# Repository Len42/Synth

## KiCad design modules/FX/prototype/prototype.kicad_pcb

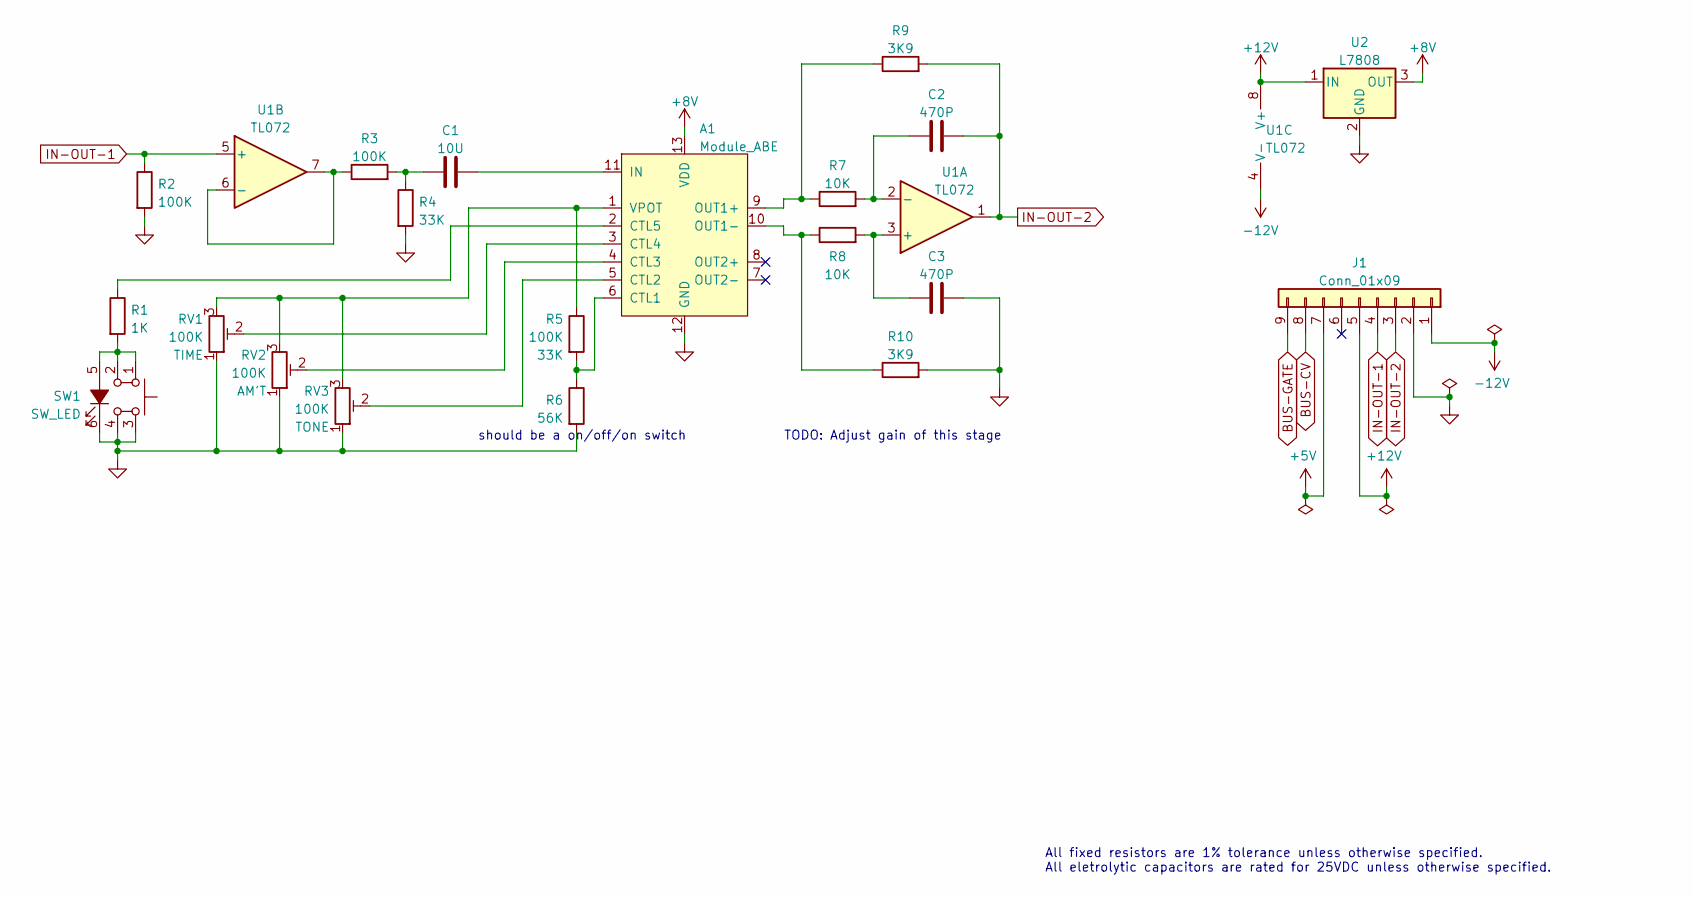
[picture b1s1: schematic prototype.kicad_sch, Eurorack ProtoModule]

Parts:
A1: Module_ABE; Module_ABE_Vert; ManufacturerPartNum ABE
C1: 10U; C_Radial_D5.0mm_H5.0mm_P2.50mm; ManufacturerPartNum ECE-A1EN100UI
C2, C3: 470P; C_Disc_D5.0mm_W2.5mm_P2.50mm
J1: Conn_01x09; PinHeader_1x09_P2.54mm_Vertical
R1: 1K; SB_Gen_4; ManufacturerPartNum MFR-12*
R2: 100K; SB_Gen_1; ManufacturerPartNum MFR-12*
R3: 100K; R_Axial_DIN0207_L6.3mm_D2.5mm_P7.62mm_Horizontal; ManufacturerPartNum MFR-12*
R4: 33K; SB_Gen_1; ManufacturerPartNum MFR-12*
R5: 100K; SB_Gen_5; ManufacturerPartNum MFR-12*
R6: 56K; SB_Gen_1; ManufacturerPartNum MFR-12*
R7, R8: 10K; R_Axial_DIN0207_L6.3mm_D2.5mm_P7.62mm_Horizontal; ManufacturerPartNum MFR-12*
R9: 3K9; SB_Gen_4; ManufacturerPartNum MFR-12*
R10: 3K9; R_Axial_DIN0207_L6.3mm_D2.5mm_P7.62mm_Horizontal; ManufacturerPartNum MFR-12*
RV1, RV2, RV3: 100K; Potentiometer_Bourns_3310R_Top
SW1: SW_LED; Breakout_SW_Push_LED_C&K_D6R; ManufacturerPartNum D6RLBUF1 LFS
U1: TL072; DIP-8_W7.62mm; ManufacturerPartNum TL072BCP
U2: L7808; TO-220-3_Vertical

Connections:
+5V: J1.7
+8V: A1.13 (VDD), U2.3 (OUT)
+12V: J1.5, U1.8 (V+), U2.1 (IN)
-12V: J1.1, U1.4 (V-)
BUS-CV: J1.8
BUS-GATE: J1.9
GND: A1.12 (GND), C3.2, J1.2, R2.2, R4.2, R6.2, R10.2, RV1.1, RV2.1, RV3.1, SW1.3, SW1.4, SW1.6 (K), U2.2 (GND)
IN-OUT-1: J1.4, R2.1, U1.5 (+)
IN-OUT-2: C2.2, J1.3, R9.2, U1.1
unnamed: A1.1 (VPOT), R5.1, RV1.3, RV2.3, RV3.3
unnamed: A1.2 (CTL5), R1.1
unnamed: A1.3 (CTL4), RV1.2
unnamed: A1.4 (CTL3), RV2.2
unnamed: A1.5 (CTL2), RV3.2
unnamed: A1.6 (CTL1), R5.2, R6.1
unnamed: A1.9 (OUT1+), R7.1, R9.1
unnamed: A1.10 (OUT1-), R8.1, R10.1
unnamed: A1.11 (IN), C1.2
unnamed: C1.1, R3.2, R4.1
unnamed: C2.1, R7.2, U1.2 (-)
unnamed: C3.1, R8.2, U1.3 (+)
unnamed: R1.2, SW1.1, SW1.2, SW1.5 (A)
unnamed: R3.1, U1.6 (-), U1.7

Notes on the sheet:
All fixed resistors are 1% tolerance unless otherwise specified. All eletrolytic capacitors are rated for 25VDC unless otherwise specified.
should be a on/off/on switch
TODO: Adjust gain of this stage

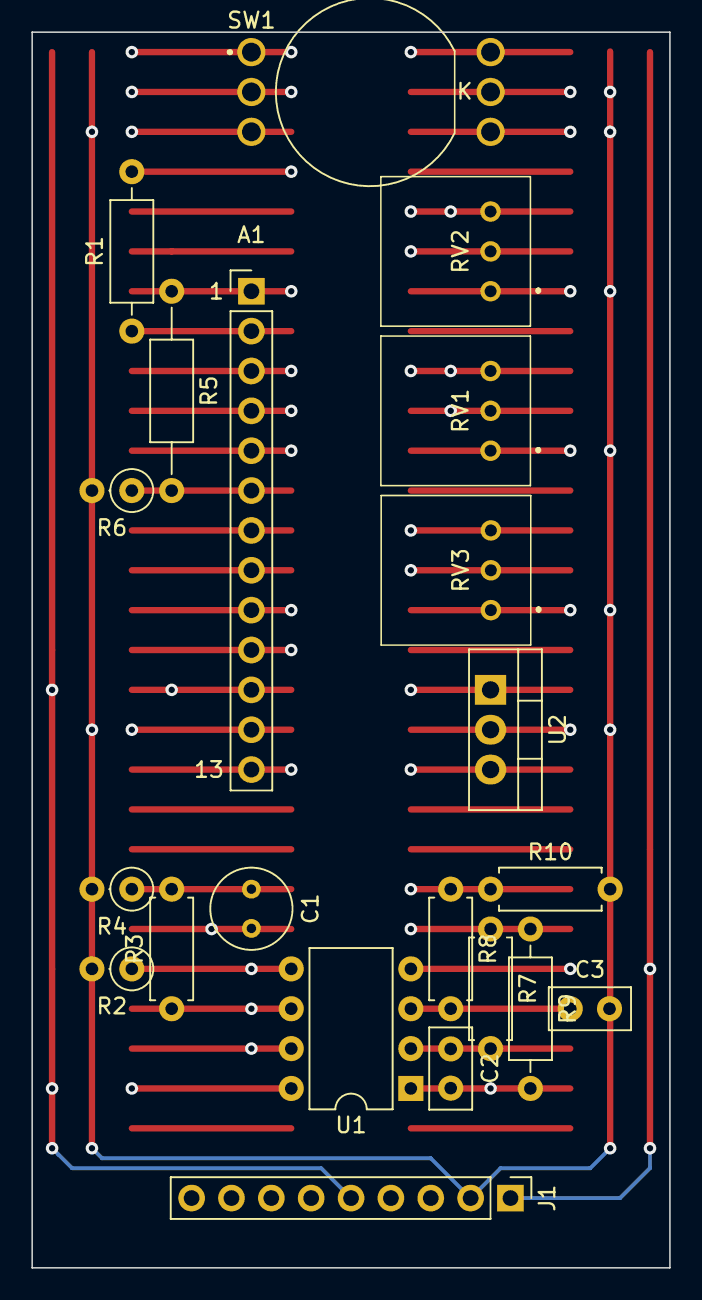
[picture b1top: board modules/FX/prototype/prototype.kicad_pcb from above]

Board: 6 copper layers, 40.6 x 78.7 mm, 21 parts (0 on the bottom side), 20 nets.

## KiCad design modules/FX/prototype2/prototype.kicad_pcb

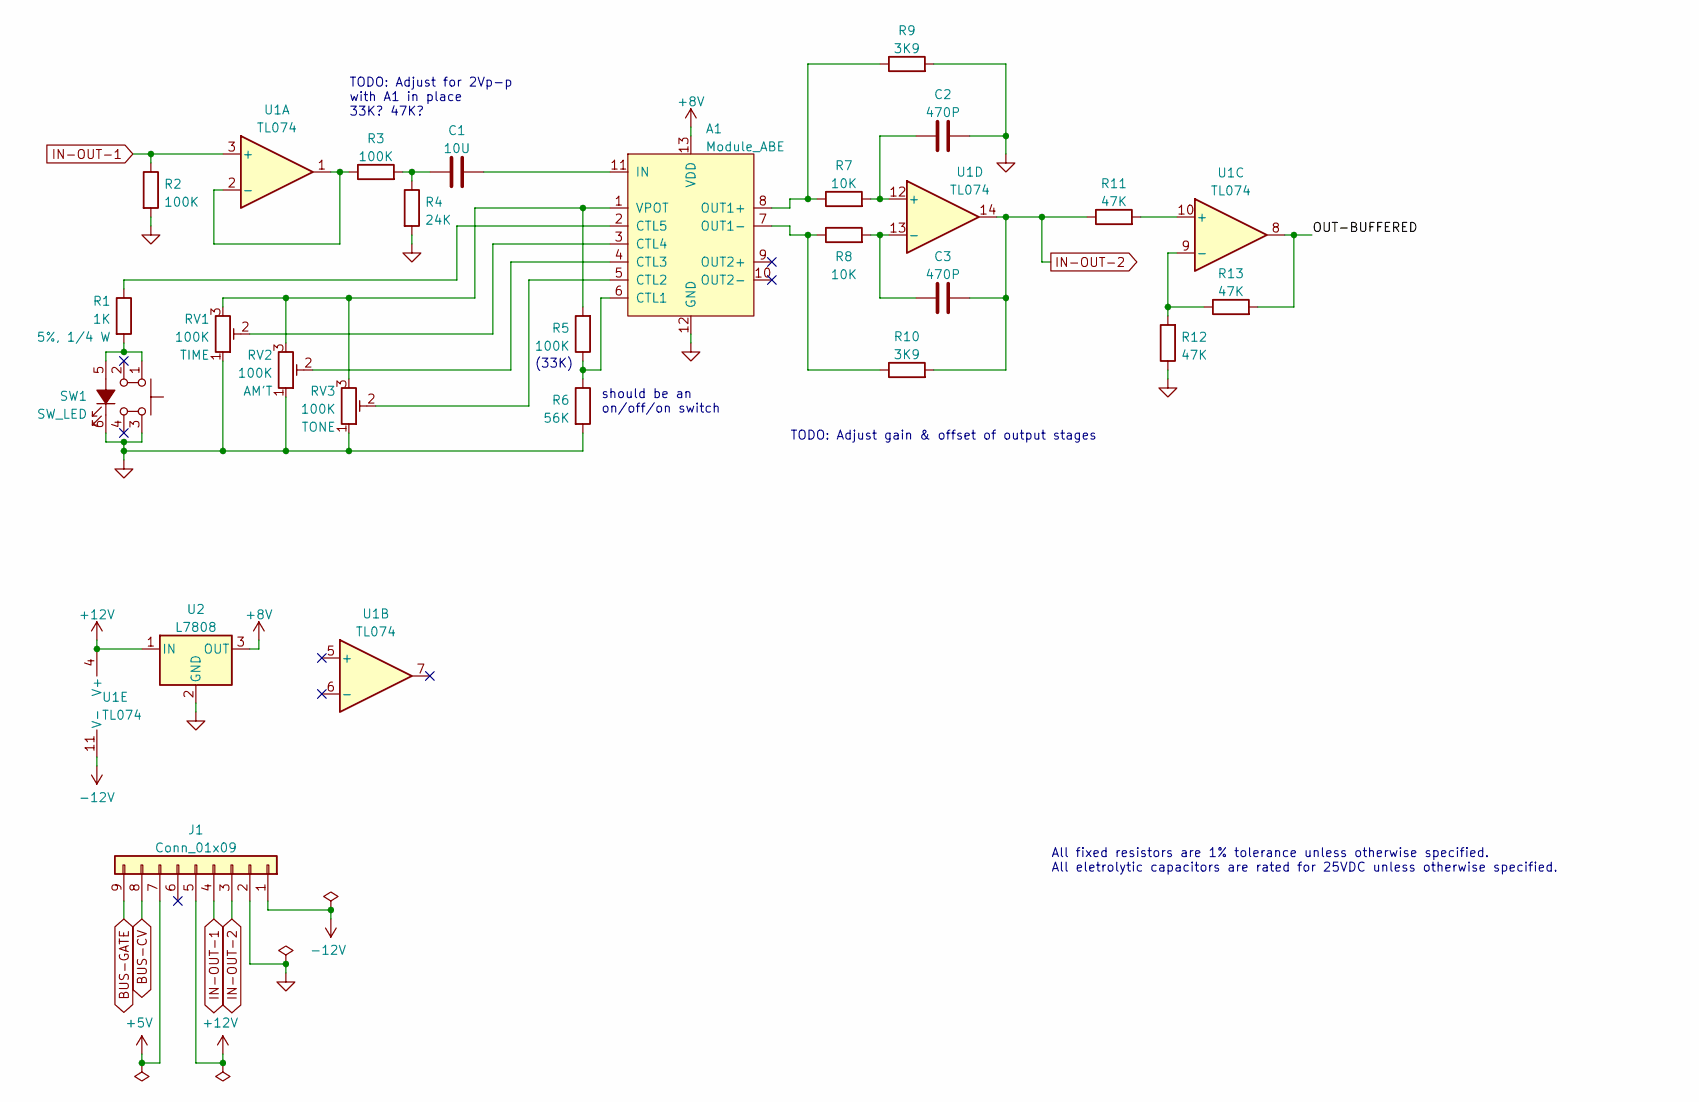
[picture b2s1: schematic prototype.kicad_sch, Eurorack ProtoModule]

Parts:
A1: Module_ABE; Module_ABE_Vert; ManufacturerPartNum ABE
C1: 10U; C_Radial_D5.0mm_H5.0mm_P2.50mm; ManufacturerPartNum ECE-A1EN100UI
C2, C3: 470P; C_Disc_D5.0mm_W2.5mm_P2.50mm
J1: Conn_01x09; PinHeader_1x09_P2.54mm_Vertical
R1: 1K; R_Axial_DIN0207_L6.3mm_D2.5mm_P10.16mm_Horizontal; ManufacturerPartNum CCF071K00JKE36
R2: 100K; SB_Gen_1; ManufacturerPartNum MFR-12*
R3: 100K; R_Axial_DIN0207_L6.3mm_D2.5mm_P7.62mm_Horizontal; ManufacturerPartNum MFR-12*
R4: 24K; SB_Gen_1; ManufacturerPartNum MFR-12*
R5: 100K; SB_Gen_5; ManufacturerPartNum MFR-12*
R6: 56K; SB_Gen_1; ManufacturerPartNum MFR-12*
R7: 10K; SB_Gen_4; ManufacturerPartNum MFR-12*
R8: 10K; R_Axial_DIN0207_L6.3mm_D2.5mm_P7.62mm_Horizontal; ManufacturerPartNum MFR-12*
R9: 3K9; SB_Gen_1; ManufacturerPartNum MFR-12*
R10: 3K9; SB_Gen_2; ManufacturerPartNum MFR-12*
R11, R12, R13: 47K; R_Axial_DIN0207_L6.3mm_D2.5mm_P7.62mm_Horizontal; ManufacturerPartNum MFR-12*
RV1, RV2: 100K; Potentiometer_Bourns_3310R_Top
RV3: 100K; Potentiometer_Bourns_3386P_Top
SW1: SW_LED; Breakout_SW_Push_LED_C&K_D6R; ManufacturerPartNum D6RLBUF1 LFS
U1: TL074; DIP-14_W7.62mm; ManufacturerPartNum TL074BCN
U2: L7808; TO-220-3_Vertical

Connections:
+5V: J1.7
+8V: A1.13 (VDD), U2.3 (OUT)
+12V: J1.5, U1.4 (V+), U2.1 (IN)
-12V: J1.1, U1.11 (V-)
/OUT-BUFFERED: R13.2, U1.8
BUS-CV: J1.8
BUS-GATE: J1.9
GND: A1.12 (GND), C2.2, J1.2, R2.2, R4.2, R6.2, R9.2, R12.1, RV1.1, RV2.1, RV3.1, SW1.3, SW1.6 (K), U2.2 (GND)
IN-OUT-1: J1.4, R2.1, U1.3 (+)
IN-OUT-2: C3.2, J1.3, R10.2, R11.1, U1.14
unnamed: A1.1 (VPOT), R5.2, RV1.3, RV2.3, RV3.3
unnamed: A1.2 (CTL5), R1.1
unnamed: A1.3 (CTL4), RV1.2
unnamed: A1.4 (CTL3), RV2.2
unnamed: A1.5 (CTL2), RV3.2
unnamed: A1.6 (CTL1), R5.1, R6.1
unnamed: A1.7 (OUT1-), R8.1, R10.1
unnamed: A1.8 (OUT1+), R7.1, R9.1
unnamed: A1.11 (IN), C1.2
unnamed: C1.1, R3.2, R4.1
unnamed: C2.1, R7.2, U1.12 (+)
unnamed: C3.1, R8.2, U1.13 (-)
unnamed: R1.2, SW1.1, SW1.5 (A)
unnamed: R3.1, U1.1, U1.2 (-)
unnamed: R11.2, U1.10 (+)
unnamed: R12.2, R13.1, U1.9 (-)

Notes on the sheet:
(33K)
TODO: Adjust for 2Vp-p with A1 in place 33K? 47K?
All fixed resistors are 1% tolerance unless otherwise specified. All eletrolytic capacitors are rated for 25VDC unless otherwise specified.
should be an on/off/on switch
TODO: Adjust gain & offset of output stages

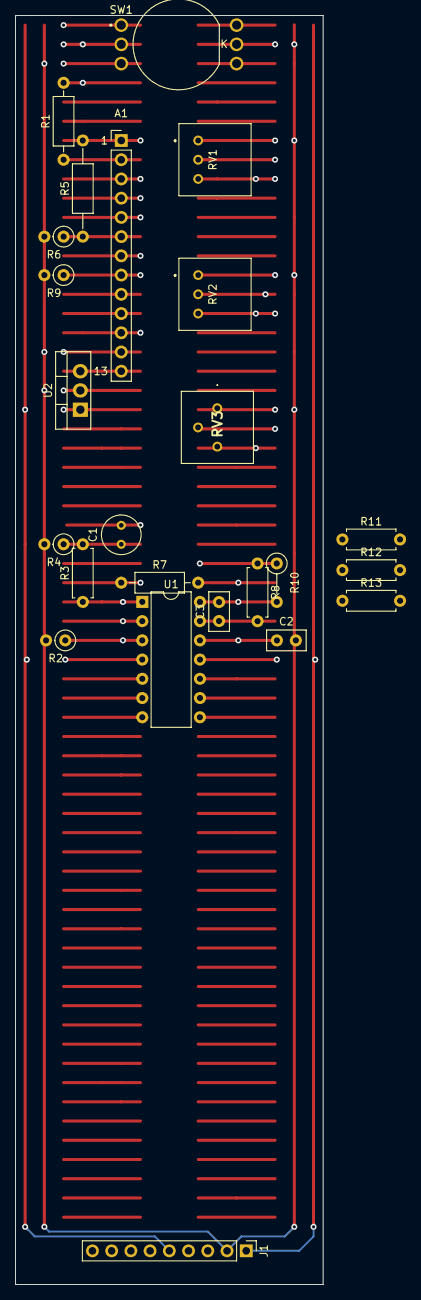
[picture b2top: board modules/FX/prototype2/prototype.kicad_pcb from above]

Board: 6 copper layers, 40.6 x 167.6 mm, 24 parts (0 on the bottom side), 23 nets.

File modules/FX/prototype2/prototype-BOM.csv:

Ref,Qty,Value,Value2,Note,Description,Datasheet,Manufacturer,ManuPartNum,Distributor1,DistributorPartNum1,DistributorPartLink1
"A1","1","Module_ABE","","","Accu-Bell Effector digital effects module","https://www.tubesandmore.com/sites/default/files/associated_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","Accu-Bell","ABE","Antique Electronic Supply","P-R-ABE","https://www.tubesandmore.com/products/dsp-module-abe-accu-be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"
"C1","1","10U","","Non-polarized","Capacitor - Non-polarized Electrolytic","https://www.mouser.ca/datasheet/2/315/ABA0000C1053-947510.pdf","Panasonic","ECE-A1EN100UI","Mouser","667-ECE-A1EN100UI","https://www.mouser.ca/ProductDetail/Panasonic/ECE-A1EN100UI?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"
"C2 C3","2","470P","","","Capacitor - Ceramic","","","","","",""
"R1","1","1K","5%, 1/4 W","Output limiting","Resistor","https://www.mouser.ca/datasheet/2/427/ccf07-1762725.pdf","Vishay / Dale","CCF071K00JKE36","Mouser","71-CCF071K00JKE36","https://www.mouser.ca/ProductDetail/Vishay-Dale/CCF071K00JKE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"
"R2 R3 R5","3","100K","1%, 1/6 W","","Resistor","https://www.mouser.ca/datasheet/2/447/Yageo_LR_MFR_1-1714151.pdf","YAGEO","MFR-12*","Mouser","603-MFR-12*","https://www.mouser.ca/c/?m=YAGEO&power+rating=166+mW+(1%2f6+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"
"R4","1","24K","1%, 1/6 W","","Resistor","https://www.mouser.ca/datasheet/2/447/Yageo_LR_MFR_1-1714151.pdf","YAGEO","MFR-12*","Mouser","603-MFR-12*","https://www.mouser.ca/c/?m=YAGEO&power+rating=166+mW+(1%2f6+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"
"R6","1","56K","1%, 1/6 W","","Resistor","https://www.mouser.ca/datasheet/2/447/Yageo_LR_MFR_1-1714151.pdf","YAGEO","MFR-12*","Mouser","603-MFR-12*","https://www.mouser.ca/c/?m=YAGEO&power+rating=166+mW+(1%2f6+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"
"R7 R8","2","10K","1%, 1/6 W","","Resistor","https://www.mouser.ca/datasheet/2/447/Yageo_LR_MFR_1-1714151.pdf","YAGEO","MFR-12*","Mouser","603-MFR-12*","https://www.mouser.ca/c/?m=YAGEO&power+rating=166+mW+(1%2f6+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"
"R9 R10","2","3K9","1%, 1/6 W","","Resistor","https://www.mouser.ca/datasheet/2/447/Yageo_LR_MFR_1-1714151.pdf","YAGEO","MFR-12*","Mouser","603-MFR-12*","https://www.mouser.ca/c/?m=YAGEO&power+rating=166+mW+(1%2f6+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"
"R11 R12 R13","3","47K","1%, 1/6 W","","Resistor","https://www.mouser.ca/datasheet/2/447/Yageo_LR_MFR_1-1714151.pdf","YAGEO","MFR-12*","Mouser","603-MFR-12*","https://www.mouser.ca/c/?m=YAGEO&power+rating=166+mW+(1%2f6+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"
"RV1 RV2 RV3","3","100K","","","Trim-potentiometer","","","","","",""
"SW1","1","SW_LED","","","Push button switch with single LED, C&K D6R series","https://www.mouser.ca/datasheet/2/60/d6-1382571.pdf","C&K","D6RLBUF1 LFS","Mouser","611-D6RLBUF1LFS","https://www.mouser.co.uk/ProductDetail/CK/D6RLBUF1-LFS?qs=zW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"
"U1","1","TL074","","","Quad Low-Noise JFET-Input Operational Amplifiers, DIP-14/SOIC-14","http://www.ti.com/lit/ds/symlink/tl071.pdf","Texas Instruments","TL074BCN","Mouser","595-TL074BCN","https://www.mouser.ca/ProductDetail/?qs=vxEfx8VrU7BHurOY5iQd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"
"U2","1","L7808","","","Positive 1.5A 35V Linear Regulator, Fixed Output 8V, TO-220/TO-263/TO-252","http://www.st.com/content/ccc/resource/technical/document/da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","","","","",""

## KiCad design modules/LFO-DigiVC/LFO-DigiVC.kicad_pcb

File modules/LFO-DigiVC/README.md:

# Voltage-Controlled Digital LFO

## 4HP Eurorack Module

### Features
- LFO rate from approximately 0.06 Hz (17 seconds) to 220 Hz (A3)
- CV input for LFO rate, with attenuator
- Three simultaneous waveform outputs, switchable between:
    - triangle, ramp, and square; or
	- three sine waves, 120° out of phase

### Notes
(I have also made a [dual analog LFO](https://github.com/Len42/Synth/tree/main/modules/LFO-Analog#readme) without voltage control.)

With the CV attenuator turned all the way up, the CV input tracks 1 volt/octave. The LFO can play notes up to A3 (below middle C) but it's fiddly to tune.

The LFO is implemented with an Arduino-compatible ATmega328P microcontroller. The firmware source code is an Arduino sketch in [firmware/DigiLFO/DigiLFO.ino](firmware/DigiLFO/DigiLFO.ino). MakeLookupTables is a program that generates data tables used in the firmware. See [here](https://lenp.net/synth/firmware-programming.html) for info about programming the firmware onto the microcontroller chip.

This module is built using the [Delptronics Module Construction Set](https://delptronics.com/module-construction-set.php) which includes PCBs for the front panel controls and other components. The PCB layout file is just a guide showing how I placed the components on the Delptronics boards. (It's a bit of a mess - sorry!)

There is a [parts list](LFO-DigiVC-BOM.csv) in spreadsheet-friendly text format.

Please note that I am a hobbyist, not a trained electronics engineer. No guarantees!

### Software Used
* [KiCad](https://www.kicad.org/) 5.1.10-1
* [Arduino](https://www.arduino.cc/) 1.8.18
* (optional) [Visual Studio 2019](https://visualstudio.microsoft.com/) - Only used to generate the numtables.h file, which is provided.

<hr /><div><div style="float:left; padding-right:10px;"></div><div style="padding-left:10px;">© 2022 Len Popp<br />This work is licensed under a <a rel="license" href="http://creativecommons.org/licenses/by/4.0/">Creative Commons Attribution 4.0 International License</a>.</div></div>

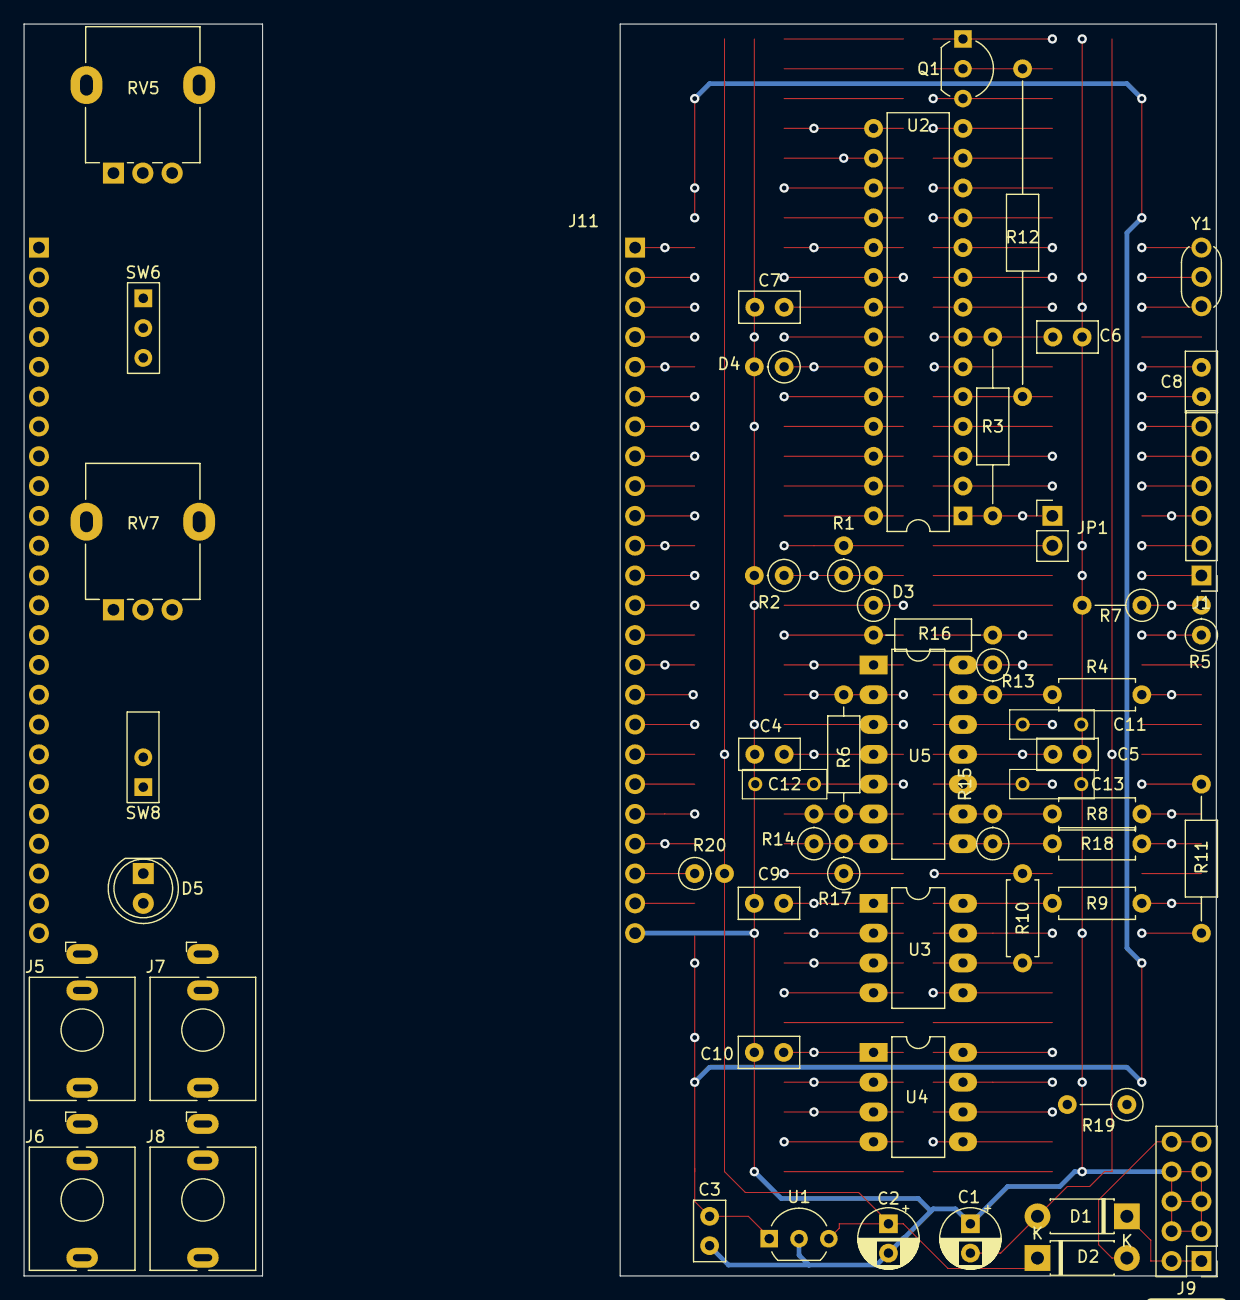
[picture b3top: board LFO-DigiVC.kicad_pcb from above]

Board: 6 copper layers, 50.8 x 106.7 mm, 58 parts (1 on the bottom side), 65 nets.

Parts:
C1, C2: 10U; CP_Radial_D5.0mm_P2.50mm
C3, C4, C5, C6, C7, C8, C9, C10: 100N; C_Disc_D5.0mm_W2.5mm_P2.50mm
C11, C12, C13: 3N3; C_Rect_Kemet_L7.2mm_W2.5mm_P5mm
D1, D2: MBR150; D_DO-41_SOD81_P7.62mm_Horizontal
D3, D4: 1N5711; SB_Gen_1
D5: VAOL-5LSBY1; LED_D5.0mm
J1: FTDI USB-TTL; PinHeader_1x06_P2.54mm_Vertical
J5, J6, J7, J8: WQP-PJ398; Jack_3.5mm_QingPu_WQP-PJ398SM_Vertical
J9: Eurorack_10; PinHeader-Eurorack-10-TH
J10: Conn_Front; PinSocket_Delptronics_Front
J11: Conn_Back; PinHeader_Delptronics_Back_Left_4HP
JP1: RESET; PinHeader_1x02_P2.54mm_Vertical
Q1: 2N3904; TO-92_Inline_Wide
R1, R2: 100K; SB_Gen_1
R3: 10K; SB_Gen_6
R4, R8: 20K; R_Axial_DIN0207_L6.3mm_D2.5mm_P7.62mm_Horizontal
R5: 10K; SB_Gen_1
R6: 20K; SB_Gen_4
R7: 20K; SB_Gen_2
R9, R10: 47K; R_Axial_DIN0207_L6.3mm_D2.5mm_P7.62mm_Horizontal
R11: 47K; SB_Gen_5
R12: 10K; SB_Gen_11
R13, R14, R15: 30K; SB_Gen_1
R16: 1K; R_Axial_DIN0207_L6.3mm_D2.5mm_P10.16mm_Horizontal
R17, R20: 1K; SB_Gen_1
R18: 1K; R_Axial_DIN0207_L6.3mm_D2.5mm_P7.62mm_Horizontal
R19: 100K; SB_Gen_2
RV5, RV7: 100K; Potentiometer_Alpha_RD901F-40-00D_Single_Vertical
SW6: ON_OFF_ON; SW_SPDT_THT_2.54
SW8: SPST; SW_SPST_THT_2.54
U1: L78L05_TO92; TO-92_Inline_Wide
U2: ATmega328P-PU; DIP-28_W7.62mm
U3: MCP4822; DIP-8_W7.62mm_LongPads
U4: MCP4821; DIP-8_W7.62mm_LongPads
U5: TL074; DIP-14_W7.62mm_LongPads
Y1: 16MHz; Resonator_muRata_CSTLSxxxX-3Pin_W5.5mm_H3.0mm

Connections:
+5V: C3.1, C6.1, C9.2, C10.2, D3.1, J1.3, J11.1, R3.1, R5.1, R19.1, U1.1, U2.7, U2.20, U3.1, U4.1
+12V: C2.1, C4.1, D2.1, R20.2, U1.3, U5.4
-12V: C1.2, C5.2, D1.2, U5.11
/Main/CV-IN-2: D3.2, D4.1, R1.1, R2.1, U2.23
/Main/SPI-MOSI: U2.17, U3.4, U4.4
/Main/SPI-SCLK: U2.19, U3.3, U4.3
/Main/VREF: R4.2, R6.2, R8.2, U5.1, U5.2
/Main/~LDAC: U2.14, U3.5, U4.5
/Main/~SPI-CS-1: U2.15, U3.2
/Main/~SPI-CS-2: U2.16, U4.2
GND: C1.1, C2.2, C3.2, C4.2, C5.1, C6.2, C7.2, C9.1, C10.1, C11.2, C12.2, C13.2, D4.2, J1.1, J1.2, J5.S, J6.S, J7.S, J8.S, J9.3, J9.4, J9.5, J9.6, J9.7, J9.8, J10.24, J11.3, J11.4, J11.7, J11.13, J11.17, J11.24, JP1.2, Q1.1, R2.2, R7.2, U1.2, U2.8, U2.22, U3.7, U4.7, Y1.2
IN-2: J11.5, J11.11
IN-SW-FUNCTION: J11.16, U2.12
IN-SW-RANGE-HI: J11.8, U2.11
IN-SW-RANGE-LO: J11.6, U2.6
LED-A: J11.22, R20.1
LED-C: J11.21, Q1.3
unnamed: C7.1, U2.21
unnamed: C8.1, J1.6
unnamed: C8.2, JP1.1, R3.2, U2.1
unnamed: C11.1, R9.1, U5.12
unnamed: C12.1, R10.1, U5.5
unnamed: C13.1, R11.1, U5.10
unnamed: D1.1, J9.1, J9.2
unnamed: D2.2, J9.9, J9.10
unnamed: D5.1, J10.21
unnamed: D5.2, J10.22
unnamed: J1.4, U2.2
unnamed: J1.5, U2.3
unnamed: J10.1, RV5.3
unnamed: J10.2, RV5.2
unnamed: J10.3, RV5.1
unnamed: J5.TN, J10.4
unnamed: J5.T, J10.5
unnamed: J10.6, SW6.1
unnamed: J10.7, SW6.2
unnamed: J10.8, SW6.3
unnamed: J6.T, J10.10
unnamed: J10.11, RV7.3
unnamed: J10.12, RV7.2
unnamed: J10.13, RV7.1
unnamed: J7.T, J10.15
unnamed: J10.16, SW8.2
unnamed: J10.17, SW8.1
unnamed: J8.T, J10.20
unnamed: Q1.2, R12.1
unnamed: R5.2, R7.1, U5.3
unnamed: R9.2, U3.8
unnamed: R10.2, U3.6
unnamed: R11.2, U4.8
unnamed: R12.2, U2.5
unnamed: R13.1, R16.2, U5.14
unnamed: R4.1, R13.2, U5.13
unnamed: R14.1, R17.2, U5.7
unnamed: R6.1, R14.2, U5.6
unnamed: R15.1, R18.2, U5.8
unnamed: R8.1, R15.2, U5.9
unnamed: R19.2, U4.6
unnamed: U2.9, Y1.3
unnamed: U2.10, Y1.1
OUT-1: J11.10, R16.1
OUT-2: J11.15, R17.1
OUT-3: J11.20, R18.1
POT-IN-1: J11.2, U2.24
POT-IN-2: J11.12, R1.2

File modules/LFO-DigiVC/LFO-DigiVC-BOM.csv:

Ref,Qty,Name,Value,Value2,Note,Description,Datasheet,Manufacturer,ManuPartNum,Distributor1,DistributorPartNum1,DistributorPartLink1,Distributor2,DistributorPartNum2,DistributorPartLink2,Distributor3,DistributorPartNum3,DistributorPartLink3
"C1 C2","2","CP_10U","10U","25 VDC","","Capacitor - Electrolytic - 12 V decoupling","https://industrial.panasonic.com/cdbs/www-data/pdf/RDF0000/A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","Panasonic","EEA-FC1E100","Mouser","667-EEA-FC1E100","https://www.mouser.ca/ProductDetail/Panasonic/EEA-FC1E100?qs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"
"C3 C4 C5 C6 C7 C8 C9 C10","8","CC_100N","100N","","IC decoupling","Capacitor - Ceramic - IC decoupling","https://product.tdk.com/system/files/dam/doc/product/capacit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","TDK","FG18X7R1H104KNT06","Mouser","810-FG18X7R1H104KNT6","https://www.mouser.ca/ProductDetail/810-FG18X7R1H104KNT6"
"C11 C12 C13","3","CF","3N3","","","Capacitor - Film","https://www.mouser.ca/datasheet/2/212/F3294_MMK-1101858.pdf","KEMET","MMK5102J100J01L16.5TA18","Mouser","80-MMK5102J100J1TA18","https://www.mouser.ca/ProductDetail/KEMET/MMK5102J100J01L165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"
"D1 D2","2","MBR150","MBR150","","","Schottky rectifier diode","https://www.onsemi.com/pdf/datasheet/mbr150-d.pdf","On Semi","MBR150RLG","Mouser","863-MBR150RLG","https://www.mouser.ca/ProductDetail/ON-Semiconductor/MBR150R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"
"D3 D4","2","1N5711","1N5711","","","Schottky signal diode","https://www.mouser.ca/datasheet/2/389/cd00000759-1795802.pdf","STMicroelectronics","1N5711","Mouser","511-1N5711","https://www.mouser.ca/ProductDetail/STMicroelectronics/1N571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"
"D5","1","LED_5mm_Blue","VAOL-5LSBY1","","","Blue Light Emitting Diode","https://www.mouser.ca/datasheet/2/423/VAOL-5LSBY1-1064871.pdf","VCC","VAOL-5LSBY1","Mouser","593-VAOL-5LSBY1","https://www.mouser.ca/ProductDetail/VCC/VAOL-5LSBY1?qs=sGAEp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"
"H1","1","PCB_Delptronics_MCS_4HP","PCB_Delptronics_MCS_4HP","","PCB & panel kit","Delptronics Module Construction Set - 4HP PCB & panel kit","https://delptronics.com/module-construction-set.php","Delptronics","","Delptronics","","https://delptronics.com/module-construction-set.php","synthCube","DELPMCSMSTR","https://synthcube.com/cart/delptronics-module-construction-set","Modular Addict","","https://modularaddict.com/module-construction-set-eurorack-p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"
"J1","1","Conn_FTDI","FTDI USB-TTL","","","Pin header for FTDI USB-serial cable","","",""
"J5 J6 J7 J8","4","Jack_WQP-PJ398","WQP-PJ398","","","Audio Jack, 2 Poles (Mono / TS), Switched T Pole (Normalling), QingPu / Thonkiconn","http://www.qingpu-electronics.com/en/products/WQP-PJ398SM-362.html","QingPu / Thonk","PJ398SM / WQP518MA","Thonk","PJ398SM","https://www.thonk.co.uk/shop/thonkiconn/","SynthCube","WQP518MA","https://synthcube.com/cart/3-5mm-euro-jacks","Adafruit","4031","https://www.adafruit.com/product/4031"
"JP1","1","Jumper_2_Open","RESET","","","Jumper, 2-pole, open","","",""
"Q1","1","Q_NPN_2N3904","2N3904","","","Small Signal NPN Transistor, 0.2A Ic, 40V Vce, TO-92","https://www.onsemi.com/pub/Collateral/2N3903-D.PDF","Central Semiconductor","2N3904 PBFREE","Mouser","610-2N3904","https://www.mouser.ca/ProductDetail/Central-Semiconductor/2N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"
"R1 R2 R19","3","R","100K","","","Resistor","https://www.mouser.ca/datasheet/2/447/Yageo_LR_MFR_1-1714151.pdf","YAGEO","MFR-12FRF52-10K","Mouser","603-MFR-12FRF5210K","https://www.mouser.ca/ProductDetail/YAGEO/MFR-12FRF52-10K?qs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"
"R3 R5 R12","3","R","10K","","","Resistor","https://www.mouser.ca/datasheet/2/447/Yageo_LR_MFR_1-1714151.pdf","YAGEO","MFR-12FRF52-10K","Mouser","603-MFR-12FRF5210K","https://www.mouser.ca/ProductDetail/YAGEO/MFR-12FRF52-10K?qs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"
"R4 R6 R7 R8","4","R","20K","","","Resistor","https://www.mouser.ca/datasheet/2/447/Yageo_LR_MFR_1-1714151.pdf","YAGEO","MFR-12FTF52-20K","Mouser","603-MFR-12FTF52-20K","https://www.mouser.ca/ProductDetail/YAGEO/MFR-12FTF52-20K?qs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"
"R9 R10 R11","3","R","47K","","","Resistor","https://www.mouser.ca/datasheet/2/447/Yageo_LR_MFR_1-1714151.pdf","YAGEO","MFR-12FTF52-30K","Mouser","603-MFR-12FTF52-30K","https://www.mouser.ca/ProductDetail/YAGEO/MFR-12FTF52-30K?qs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"
"R13 R14 R15","3","R","30K","","","Resistor","https://www.mouser.ca/datasheet/2/447/Yageo_LR_MFR_1-1714151.pdf","YAGEO","MFR-12FTF52-30K","Mouser","603-MFR-12FTF52-30K","https://www.mouser.ca/ProductDetail/YAGEO/MFR-12FTF52-30K?qs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"
"R16 R17 R18 R20","4","R_1K_Output","1K","5%, 1/4 W","Output limiting","Resistor","https://www.mouser.ca/datasheet/2/427/ccf07-1762725.pdf","Vishay / Dale","CCF071K00JKE36","Mouser","71-CCF071K00JKE36","https://www.mouser.ca/ProductDetail/Vishay-Dale/CCF071K00JKE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"
"RV5","1","R_POT_Panel_PCB_Alpha","100K","LIN","","Potentiometer","https://www.mouser.ca/datasheet/2/13/alpha_taiwan_08192019_R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","Alpha","RD901F-*","Mouser","311-1940F-*","https://www.mouser.ca/c/passive-components/potentiometers-tr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"
"RV7","1","R_POT_TRIM_Panel_SongHuei","100K","LIN","","Potentiometer","http://www.song-huei.com/proimages//eng/pdfimages/R0904N.pdf","Song Huei","R0904N*","SynthCube","SH9MMTPOTMSTR","https://synthcube.com/cart/9mm-trimmer-pots"
"SW6","1","SW_SPDT_ON_OFF_ON","ON_OFF_ON","","","Switch, single pole double throw, center OFF position, toggle, submini","https://www.mouser.ca/datasheet/2/221/MS-100542-1173960.pdf","Mountain Switch","10TC412","Mouser","10TC412","https://www.mouser.ca/ProductDetail/Mountain-Switch/10TC412?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","Thonk","","https://www.thonk.co.uk/shop/sub-mini-toggle-switches/","SynthCube","","https://synthcube.com/cart/toggle-switch-submini-pc-pin"
"SW8","1","SW_SPST","SPST","","","Single Pole Single Throw (SPST) sub-mini toggle switch","https://www.mouser.ca/datasheet/2/221/MS-100542-1173960.pdf","Mountain Switch","10TC405","Mouser","10TC405","https://www.mouser.ca/ProductDetail/Mountain-Switch/10TC405?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"
"U1","1","L78L05_TO92","L78L05_TO92","","","Positive 100mA 30V Linear Regulator, Fixed Output 5V, TO-92","http://www.st.com/content/ccc/resource/technical/document/da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","STMicroelectronics ","L78L05ACZ-AP","Mouser","511-L78L05ACZ-AP","https://www.mouser.ca/ProductDetail/STMicroelectronics/L78L0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"
"U2","1","ATmega328P-PU","ATmega328P-PU","16 MHz","programmed with Arduino bootloader","20MHz, 32kB Flash, 2kB SRAM, 1kB EEPROM, DIP-28","https://www.microchip.com/en-us/product/ATmega328P","Microchip","ATMEGA328P-PU","Mouser","556-ATMEGA328P-PU","https://www.mouser.ca/ProductDetail/?qs=K8BHR703ZXguOQv3sKbW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","Adafruit","123","https://www.adafruit.com/product/123"
"U3","1","MCP4822","MCP4822","","","2-Channel 12-Bit D/A Converters with SPI Interface and Internal Reference (2.048V)","https://www.mouser.ca/datasheet/2/268/21953a-8929.pdf","Microchip","MCP4822-E/P","Mouser","579-MCP4822-E/P","https://www.mouser.ca/ProductDetail/Microchip-Technology/MCP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"
"U4","1","MCP4821","MCP4821","","","12-Bit D/A Converters with SPI Interface, internal Reference (2.048V)","http://ww1.microchip.com/downloads/en/DeviceDoc/22244B.pdf","Microchip","MCP4821-E/P","Mouser","579-MCP4821-E/P","https://www.mouser.ca/ProductDetail/Microchip-Technology/MCP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"
"U5","1","TL074","TL074","","","Quad Low-Noise JFET-Input Operational Amplifiers, DIP-14/SOIC-14","http://www.ti.com/lit/ds/symlink/tl071.pdf","Texas Instruments","TL074BCN","Mouser","595-TL074BCN","https://www.mouser.ca/ProductDetail/?qs=vxEfx8VrU7BHurOY5iQd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"
"Y1","1","Resonator_16MHz","16MHz","","","Three pin ceramic resonator, small symbol","https://www.mouser.ca/datasheet/2/281/p17e-1539077.pdf","Murata","CSTLS16M0X53Z-A0","Mouser"," 81-CSTLS16M0X53Z-A0","https://www.mouser.ca/ProductDetail/?qs=x6vGwhDZZUZCi2wdIsDb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"

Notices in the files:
modules/Adder/PanelPower.kicad_sch:
Copyright © 2022 Len Popp CC BY
modules/Audiout/PanelPower.kicad_sch:
Copyright © 2021 Len Popp CC BY
modules/Filter2/PanelPower.kicad_sch:
Copyright © 2023 Len Popp CC BY
modules/LFO-Analog/PanelPower.kicad_sch:
Copyright © 2024 Len Popp CC BY
